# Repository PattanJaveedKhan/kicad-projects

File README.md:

# kicad-projects

PROJECT 1: THREE LEDS PCB DESIGN 

https://github.com/user-attachments/assets/29c472d2-16ab-41b3-ab7c-6b4cade4d54b

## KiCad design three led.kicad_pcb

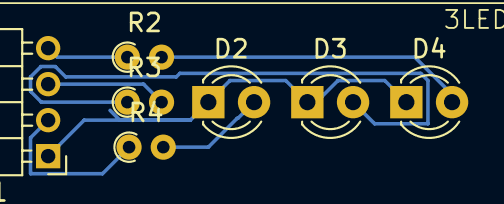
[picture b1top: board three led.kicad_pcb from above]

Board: 2 copper layers, 7 parts (0 on the bottom side), 7 nets.

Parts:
D2, D3, D4: LED; LED_D3.0mm
J1: Conn_01x04_Pin; PinHeader_1x04_P2.00mm_Horizontal
R2, R3, R4: 220; R_Axial_DIN0204_L3.6mm_D1.6mm_P1.90mm_Vertical

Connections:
unnamed: D2.2 (A), R4.2
unnamed: D2.1 (K), D3.1 (K), D4.1 (K), J1.1
unnamed: D3.2 (A), R3.1
unnamed: D4.2 (A), R2.2
unnamed: J1.2, R4.1
unnamed: J1.3, R3.2
unnamed: J1.4, R2.1

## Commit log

2025-08-31 Create 3leds pcb design
